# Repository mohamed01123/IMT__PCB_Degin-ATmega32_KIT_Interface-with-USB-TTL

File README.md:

🔧  PCB Design Project
This project is a 2-layer PCB design made to interface with a USB to TTL module and a microcontroller (ATmega32). The main goal of the project is to allow easy programming and testing of the ATmega32 using a simple USB connection and a stable power source.

🎯 Main Features:
Microcontroller: ATmega32

USB Interface: Connected through a 1x5 pin connector to any USB to TTL module

Programming: Code is burned into the ATmega32 using USB to TTL

Standalone Operation: After burning the code, the system can run independently using output power

🔌 Power Management:
A 7805 voltage regulator is used to protect the microcontroller in case the user connects a power supply higher than 5V

A Power LED is connected to show that the microcontroller is powered on

💡 Testing and Indicators:
3 LEDs are connected to Port D, pins 2, 3, and 4

These LEDs are used for testing the microcontroller's output and functionality

🔄 Connectivity:
4 x 8-pin sockets are added to connect the microcontroller’s 4 ports (Port A, B, C, D)

1 x 5-pin connector connects the USB to TTL module to the microcontroller (for RX, TX, VCC, GND, and RESET if needed)

⏱ Clock:
A 16 MHz crystal oscillator is used for accurate timing

2 capacitors are connected with the crystal to stabilize the clock signal

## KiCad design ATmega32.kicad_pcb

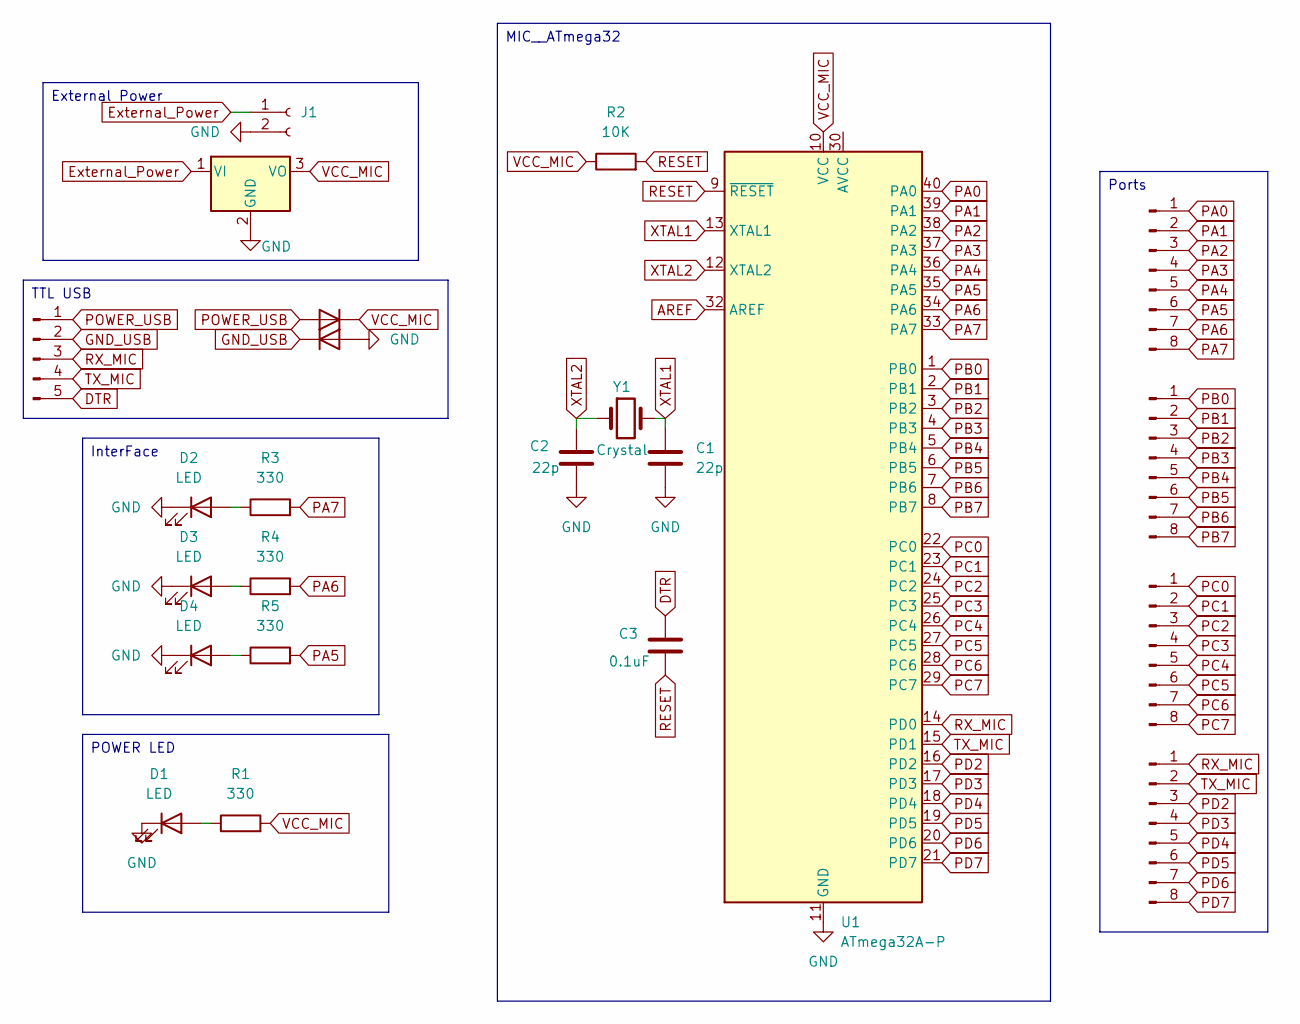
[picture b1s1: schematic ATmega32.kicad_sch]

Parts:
C1, C2: 22p; C_Radial_D4.0mm_H7.0mm_P1.50mm
C3: 0.1uF; C_Radial_D4.0mm_H7.0mm_P1.50mm
D1: LED; LED_0805_2012Metric
D2, D3, D4: LED; LED_D3.0mm
D5, D6: D; D_5W_P10.16mm_Horizontal
J1: Conn_01x02_Socket; PinSocket_1x02_P2.54mm_Vertical
J2, J4, J5, J6: Conn_01x08_Pin; PinHeader_1x08_P2.00mm_Vertical
J3: Conn_01x05_Pin; PinHeader_1x05_P2.00mm_Vertical
R1, R3, R4, R5: 330; R_Axial_DIN0207_L6.3mm_D2.5mm_P7.62mm_Horizontal
R2: 10K; R_Axial_DIN0207_L6.3mm_D2.5mm_P7.62mm_Horizontal
U1: ATmega32A-P; DIP-40_W15.24mm
U2: LM7805_TO220; TO-220-3_Vertical
Y1: Crystal; Crystal_C26-LF_D2.1mm_L6.5mm_Vertical

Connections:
AREF: U1.32 (AREF)
DTR: C3.1, J3.5
External_Power: J1.1, U2.1 (VI)
GND: C1.2, C2.2, D1.1 (K), D2.1 (K), D3.1 (K), D4.1 (K), D6.2 (A), J1.2, U1.11 (GND), U1.31 (GND), U2.2 (GND)
GND_USB: D6.1 (K), J3.2
unnamed: D1.2 (A), R1.1
unnamed: D2.2 (A), R3.1
unnamed: D3.2 (A), R4.1
unnamed: D4.2 (A), R5.1
PA0: J2.1, U1.40 (PA0)
PA1: J2.2, U1.39 (PA1)
PA2: J2.3, U1.38 (PA2)
PA3: J2.4, U1.37 (PA3)
PA4: J2.5, U1.36 (PA4)
PA5: J2.6, R5.2, U1.35 (PA5)
PA6: J2.7, R4.2, U1.34 (PA6)
PA7: J2.8, R3.2, U1.33 (PA7)
PB0: J4.1, U1.1 (PB0)
PB1: J4.2, U1.2 (PB1)
PB2: J4.3, U1.3 (PB2)
PB3: J4.4, U1.4 (PB3)
PB4: J4.5, U1.5 (PB4)
PB5: J4.6, U1.6 (PB5)
PB6: J4.7, U1.7 (PB6)
PB7: J4.8, U1.8 (PB7)
PC0: J5.1, U1.22 (PC0)
PC1: J5.2, U1.23 (PC1)
PC2: J5.3, U1.24 (PC2)
PC3: J5.4, U1.25 (PC3)
PC4: J5.5, U1.26 (PC4)
PC5: J5.6, U1.27 (PC5)
PC6: J5.7, U1.28 (PC6)
PC7: J5.8, U1.29 (PC7)
PD2: J6.3, U1.16 (PD2)
PD3: J6.4, U1.17 (PD3)
PD4: J6.5, U1.18 (PD4)
PD5: J6.6, U1.19 (PD5)
PD6: J6.7, U1.20 (PD6)
PD7: J6.8, U1.21 (PD7)
POWER_USB: D5.2 (A), J3.1
RESET: C3.2, R2.2, U1.9 (~RESET)
RX_MIC: J3.3, J6.1, U1.14 (PD0)
TX_MIC: J3.4, J6.2, U1.15 (PD1)
VCC_MIC: D5.1 (K), R1.2, R2.1, U1.10 (VCC), U1.30 (AVCC), U2.3 (VO)
XTAL1: C1.1, U1.13 (XTAL1), Y1.2
XTAL2: C2.1, U1.12 (XTAL2), Y1.1

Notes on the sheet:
TTL USB
External Power
MIC__ATmega32
InterFace
Ports
POWER LED

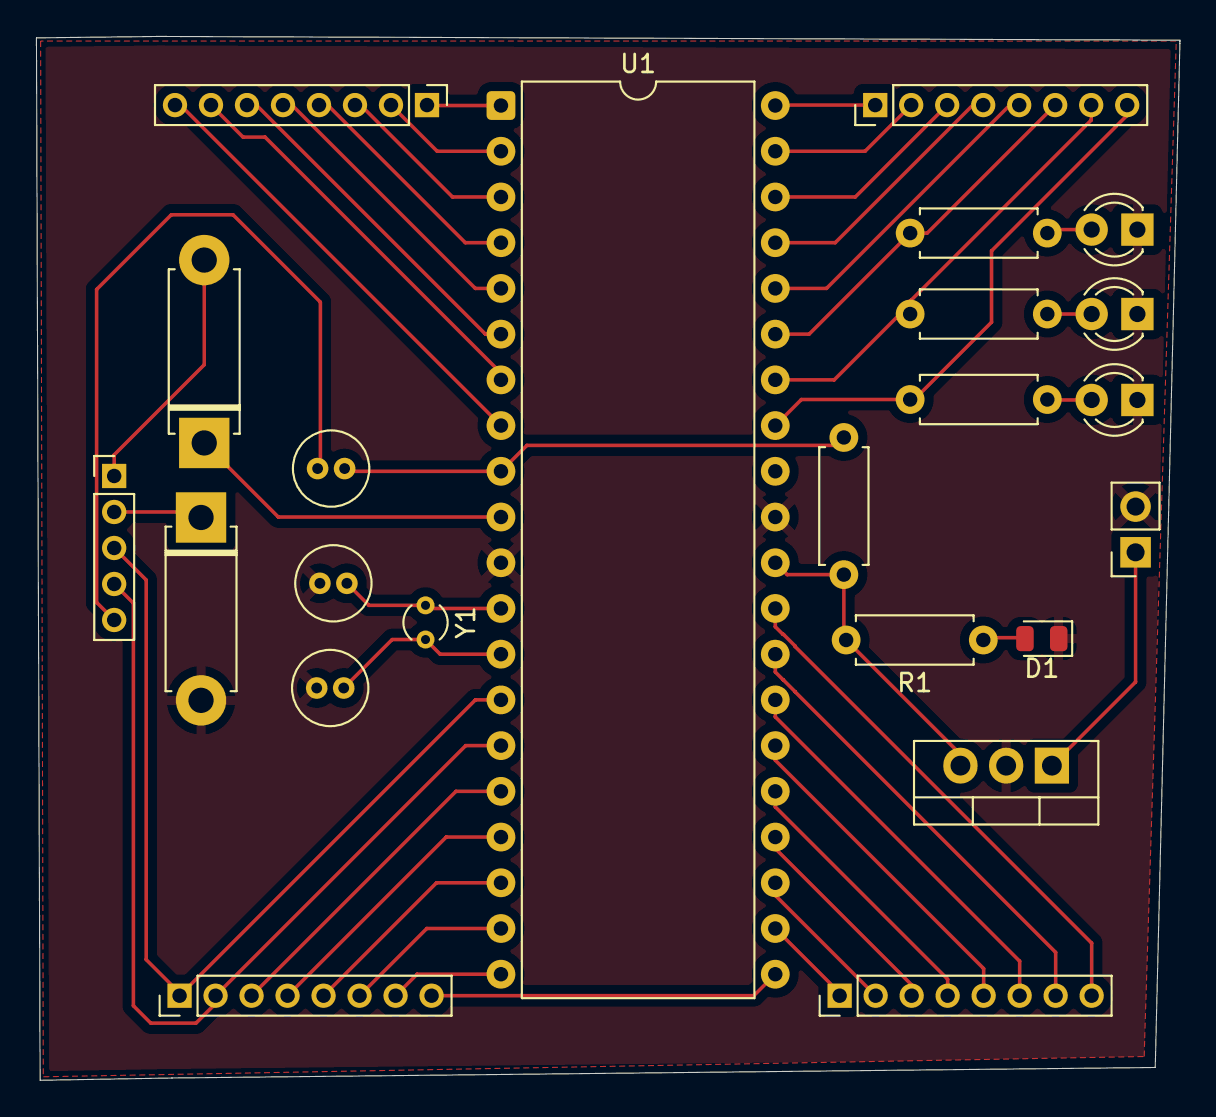
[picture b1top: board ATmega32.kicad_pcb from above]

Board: 2 copper layers, 63.5 x 58.0 mm, 23 parts (0 on the bottom side), 45 nets.

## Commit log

2025-05-22 the first commit
2025-05-22 edite tracks
2025-05-24 Edite design
